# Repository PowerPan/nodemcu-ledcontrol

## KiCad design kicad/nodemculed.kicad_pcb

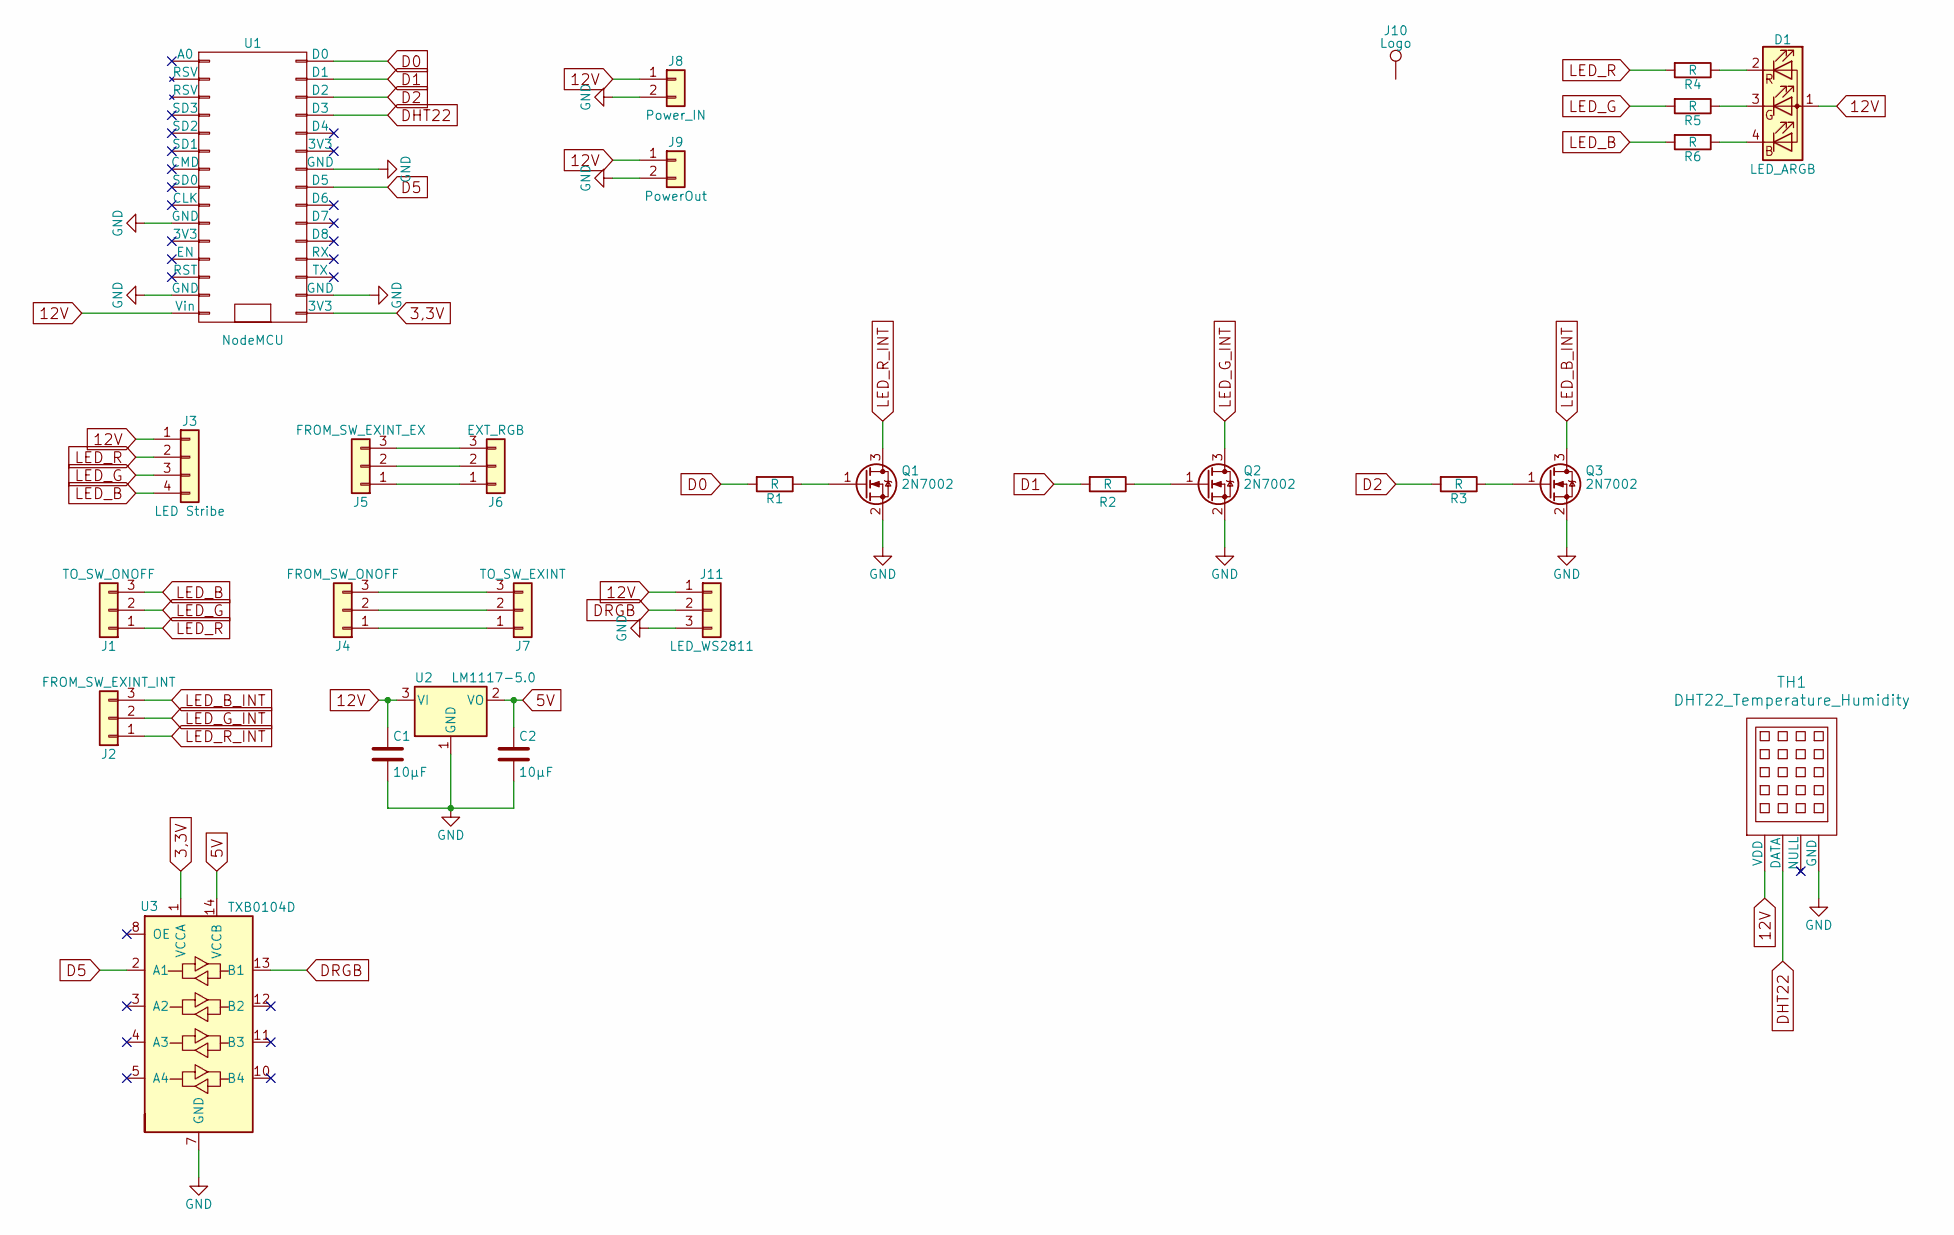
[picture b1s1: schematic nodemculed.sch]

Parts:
C1, C2: 10µF; C_1206_HandSoldering
D1: LED_ARGB; Molex_KK-6410-04_04x2.54mm_Straight
J1: TO_SW_ONOFF; Molex_KK-6410-03_03x2.54mm_Straight
J2: FROM_SW_EXINT_INT; Molex_KK-6410-03_03x2.54mm_Straight
J3: LED Stribe; Molex_KK-6410-04_04x2.54mm_Straight
J4: FROM_SW_ONOFF; Molex_KK-6410-03_03x2.54mm_Straight
J5: FROM_SW_EXINT_EX; Molex_KK-6410-03_03x2.54mm_Straight
J6: EXT_RGB; Molex_KK-6410-03_03x2.54mm_Straight
J7: TO_SW_EXINT; Molex_KK-6410-03_03x2.54mm_Straight
J8: Power_IN; Molex_KK-6410-02_02x2.54mm_Straight
J9: PowerOut; Molex_KK-6410-02_02x2.54mm_Straight
J10: Logo; diywwlogo_1cm
J11: LED_WS2811; Molex_KK-6410-03_03x2.54mm_Straight
Q1, Q2, Q3: 2N7002; SOT-23_Handsoldering
R1, R2, R3, R4, R5, R6: R; R_1206_HandSoldering
TH1: DHT22_Temperature_Humidity; Molex_KK-6410-03_03x2.54mm_Straight
U1: NodeMCU; NodeMCU_Amica_R2
U2: LM1117-5.0; SOT-223-3_TabPin2
U3: TXB0104D; SOIC-14_3.9x8.7mm_Pitch1.27mm

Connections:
3,3V: U1.16 (3V3), U3.1 (VCCA)
5V: C2.1, U2.2 (VO), U3.14 (VCCB)
12V: C1.1, D1.1 (A), J3.1, J8.1, J9.1, J11.1, TH1.1 (VDD), U1.15 (Vin), U2.3 (VI)
D0: R1.2, U1.30 (D0)
D1: R2.2, U1.29 (D1)
D2: R3.2, U1.28 (D2)
D5: U1.23 (D5), U3.2 (A1)
DHT22: TH1.2 (DATA), U1.27 (D3)
DRGB: J11.2, U3.13 (B1)
GND: C1.2, C2.2, J8.2, J9.2, J11.3, Q1.2 (S), Q2.2 (S), Q3.2 (S), TH1.4 (GND), U1.10 (GND), U1.14 (GND), U1.17 (GND), U1.24 (GND), U2.1 (GND), U3.7 (GND)
LED_B: J1.3, J3.4, R6.2
LED_B_INT: J2.3, Q3.3 (D)
LED_G: J1.2, J3.3, R5.2
LED_G_INT: J2.2, Q2.3 (D)
LED_R: J1.1, J3.2, R4.2
LED_R_INT: J2.1, Q1.3 (D)
unnamed: D1.2 (RK), R4.1
unnamed: D1.3 (GK), R5.1
unnamed: D1.4 (BK), R6.1
unnamed: J4.1, J7.1
unnamed: J4.2, J7.2
unnamed: J4.3, J7.3
unnamed: J5.1, J6.1
unnamed: J5.2, J6.2
unnamed: J5.3, J6.3
unnamed: Q1.1 (G), R1.1
unnamed: Q2.1 (G), R2.1
unnamed: Q3.1 (G), R3.1

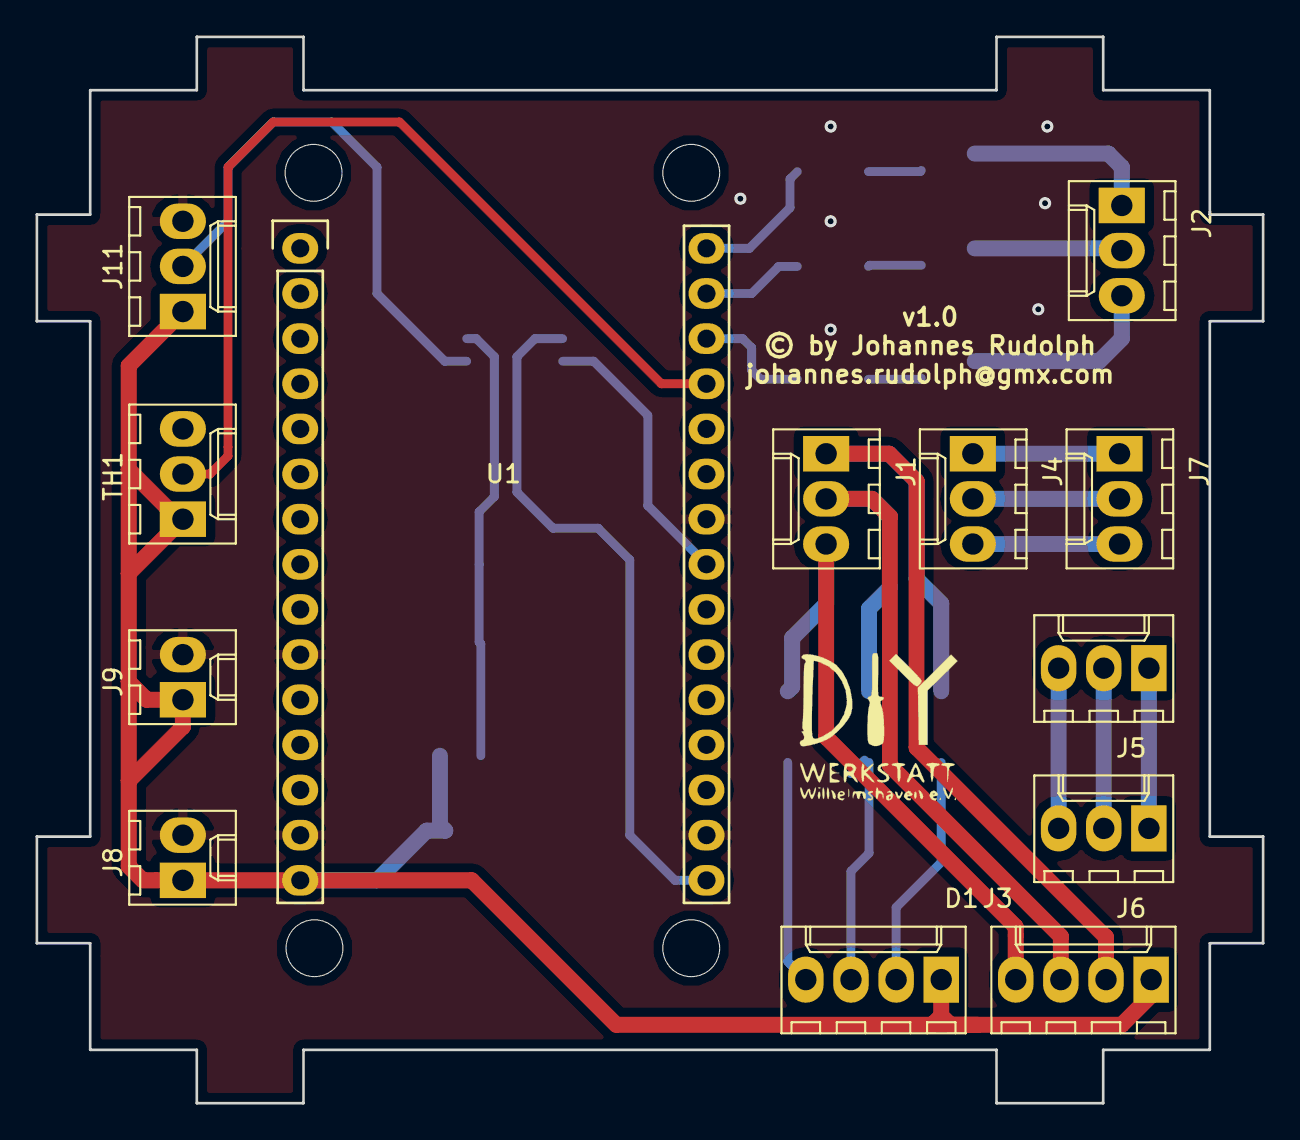
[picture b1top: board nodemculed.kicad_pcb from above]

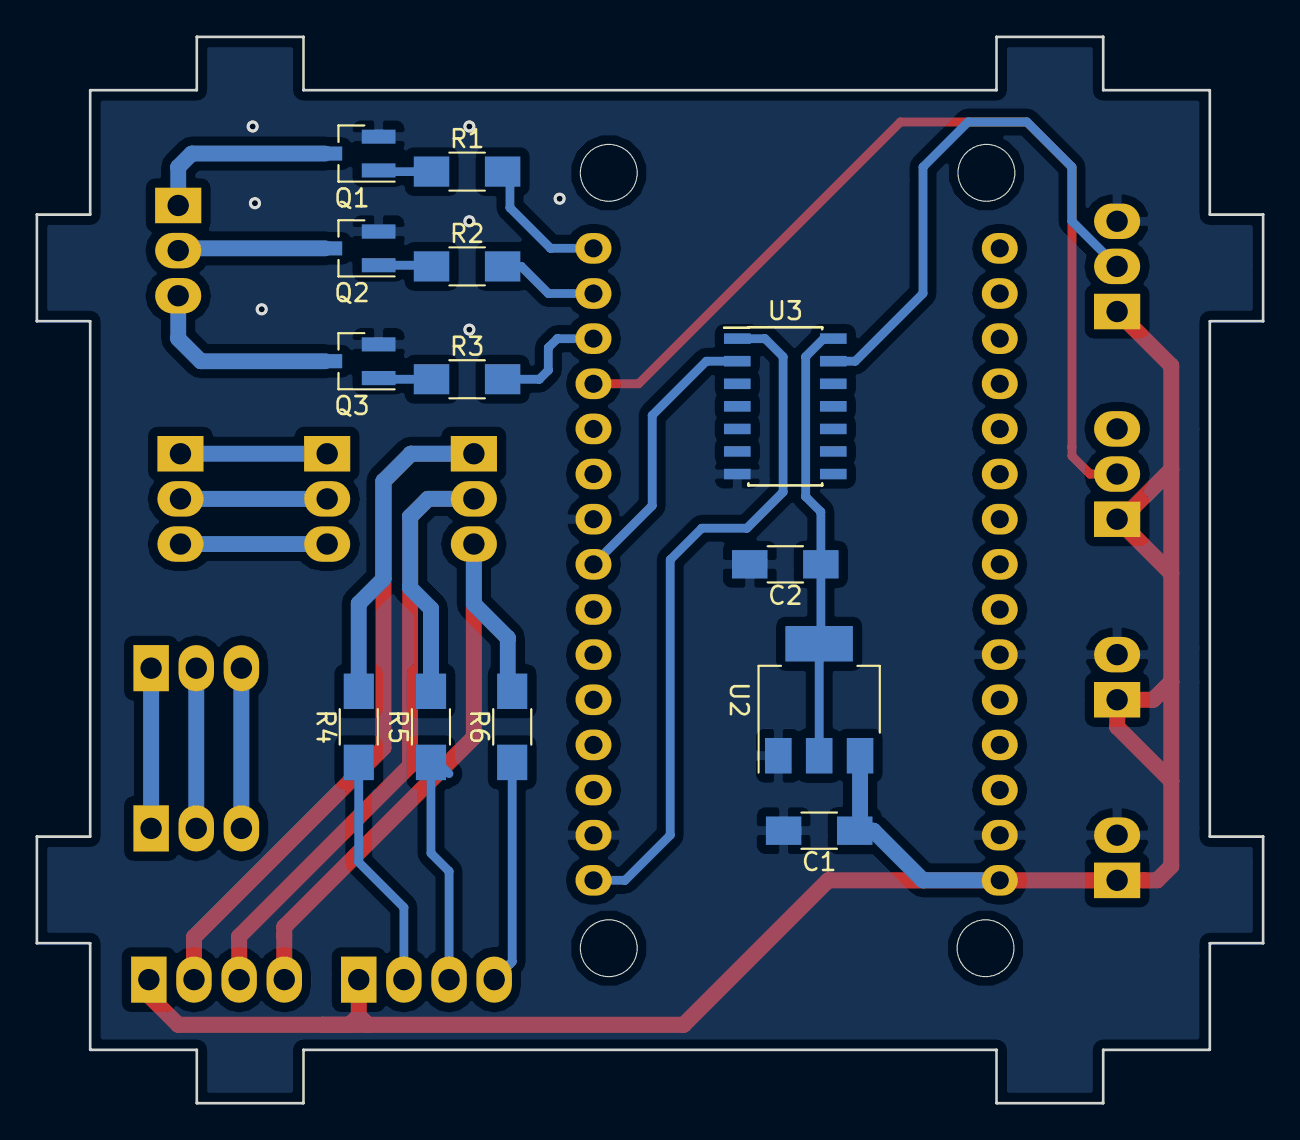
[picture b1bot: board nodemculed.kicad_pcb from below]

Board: 2 copper layers, 69.0 x 60.0 mm, 27 parts (13 on the bottom side), 28 nets.

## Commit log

2017-12-29 init PCB v1

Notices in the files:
kicad/nodemculed.kicad_pcb:
© by Johannes Rudolph
